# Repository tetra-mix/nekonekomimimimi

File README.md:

# ねこねこみみみみ
## 概要
VRCとの連携を目的として、市販されている猫耳カチューシャに取り付けられるハプティクスデバイスを作成する。ケーブル部分には、3Dプリンターで作成したケーブルチェーンを用いる。senseshift-hardwareというOSSプロジェクトを参考にしながら作成する。

## 参考
[自作ハプティクスベストを作ってみた。｜KirisameNanoha](https://note.com/kirisamenanoha/n/n8a3842eb5d57)
[GitHub - senseshift/senseshift-hardware: Hardware schematics to build haptic-feedback devices](https://github.com/senseshift/senseshift-hardware)
[OSC](https://note.com/kirisamenanoha/n/n18400ababb78?app_launch=false)
## 予備知識

### ハプティクスモーターについて
ERM 偏心回転質量
* PWAで制御
	種類
	* コイン型
	* 円筒型
	* コア型

LRA 線形共振
* 注意：ドライバが必要
	種類
	* コイン型
	* バー型
	* Y軸(平行)
	* Z軸(垂直)

## 案
### 案１
* マイコン esp32系
	* xiao esp32s3 or c6
* ドライバ DRV2605 x2
* LRAコイン型(Z軸)を直線に複数配置
* 左右の耳の下に3つずつ(計6つ)
* 電源をどうするかは検討
	* リポバッテリー？
	* 最初はモバイルバッテリーかな
→LRAが入手しづらい

### 案２ →採用
 * マイコン esp32系
	* xiao esp32s3 or c6
* ERMコイン型を直線に複数配置
* 左右の耳の下に3つずつ(計6つ)
* MOSFET x6
* 電源をどうするかは検討
	* リポバッテリー？
	* 最初はモバイルバッテリー

## 回路図
1チャンネル分
```
                 VMOTOR (+3.0V～4.2V)
                        |
                        |
                    +---+---+
                    |  ERM  |
                    |Motor  |
                    +---+---+
                        |
                        +-------------------+
                        |                   |
                        |                 |<| D1
                        |            SS14 / 1N5819
                        |                 | |
                        |                   |
                        |                   +---- VMOTOR
                        |
                      Drain
                    Q1 N-MOSFET ---- Gate
                      Source
                        |
                       GND

XIAO GPIO PWM ----[100Ω]---- Gate
                         |
                       [100kΩ]
                         |
                        GND
```

MOSFETをどれだけON・OFFするかによって強さを決める

## 配置図
```
        [前（おでこ）]

   左側               右側
   ●──●──●       ●──●──●
   前  中  後       前  中  後

        [後（後頭部）]
```

## 部品
秋月電子の場合

| 品名            | 型番                  |  個数 |    値段 | 購入リンク                                                  |
| ------------- | ------------------- | --: | ----: | ------------------------------------------------------ |
| DMOSトランジスタアレイ | TBD62003APG         |   1 |   100 | [109943](https://akizukidenshi.com/catalog/g/g109943/) |
| ミニ振動モーター      | (記載なし / 秋月ミニ振動モーター) |   6 |   200 | [16777](https://akizukidenshi.com/catalog/g/g116777/)  |
| マイコンボード       | XIAO ESP32S3        |   1 | 1,480 | [118078](https://akizukidenshi.com/catalog/g/g118078/) |
| ショットキーダイオード   | 1S4                 |   1 |   140 | [116384](https://akizukidenshi.com/catalog/g/g116384/) |
| 電解コンデンサ       | 1000µF（耐圧10V〜）      |   1 |    20 | [108424](https://akizukidenshi.com/catalog/g/g108424/) |
| LDO 3.3V1A    | BA033CC0T           |   1 |   100 | [113675](https://akizukidenshi.com/catalog/g/g113675/) |

合計3220円

振動モーターはアリエクで買ってもいいかも？

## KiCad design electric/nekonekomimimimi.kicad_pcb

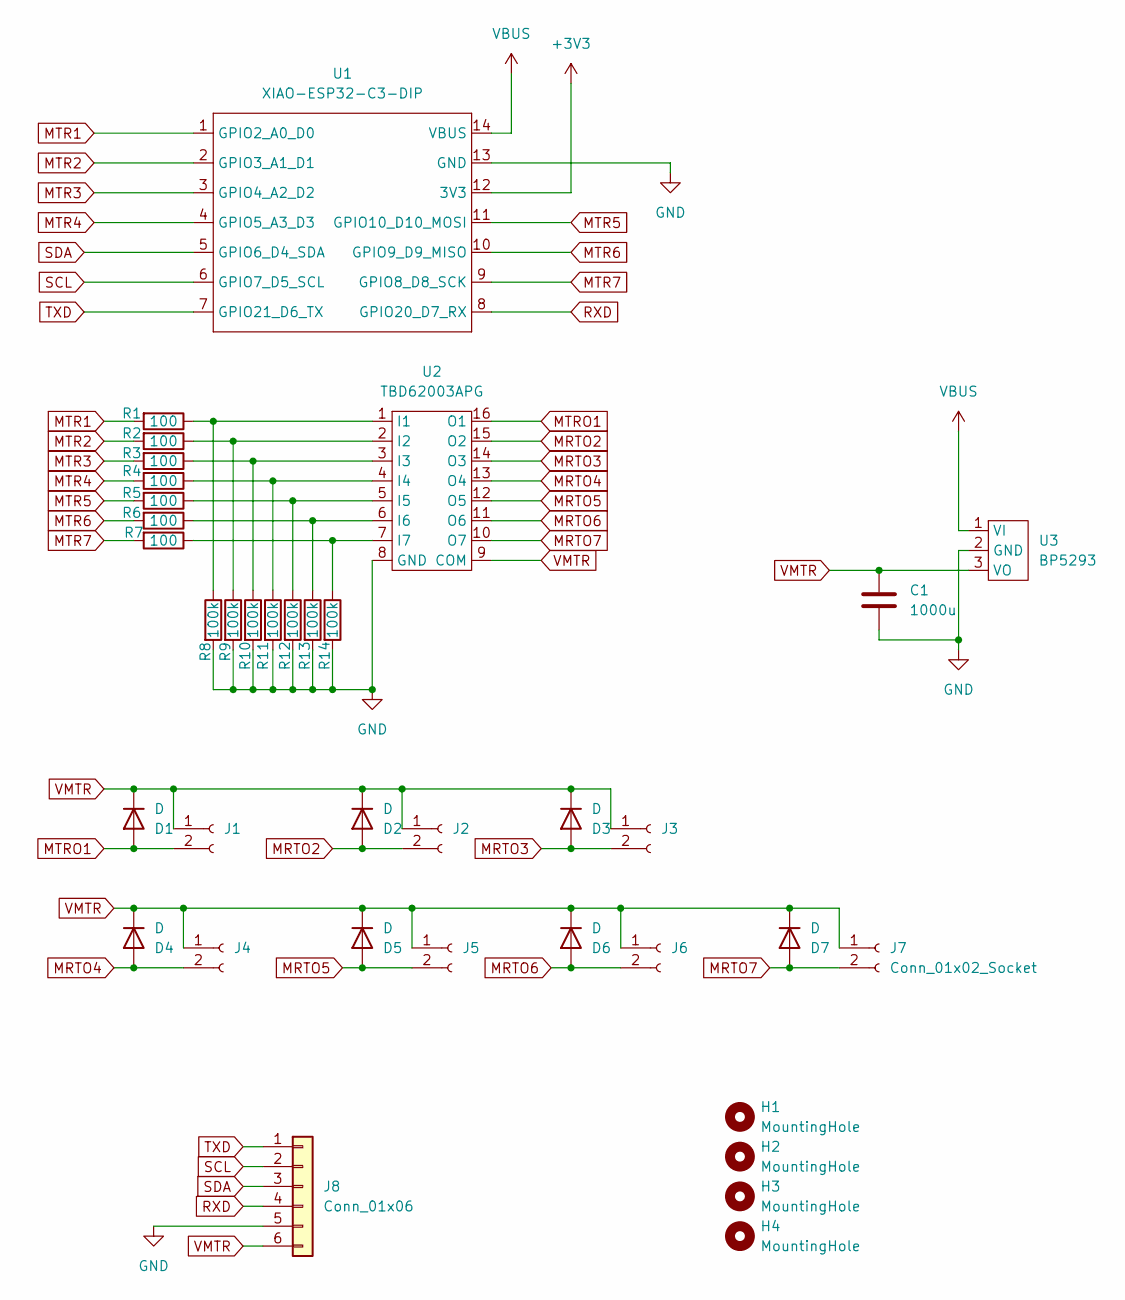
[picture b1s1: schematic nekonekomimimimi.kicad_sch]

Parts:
C1: 1000u; CP_Radial_D10.0mm_P5.00mm
D1, D2, D3, D4, D5, D6, D7: D; D_DO-35_SOD27_P7.62mm_Horizontal
H1, H2, H3, H4: MountingHole; MountingHole_2.2mm_M2
J1, J2, J3, J4, J5, J6, J7: Conn_01x02_Socket; JST_XH_B2B-XH-A_1x02_P2.50mm_Vertical
J8: Conn_01x06; PinHeader_1x06_P2.54mm_Vertical
R1, R2, R3, R4, R5, R6, R7: 100; resistor_0207_10
R8, R9, R10, R11, R12, R13, R14: 100k; resistor_0207_10
U1: XIAO-ESP32-C3-DIP; XIAO-ESP32-C6-DIP
U2: TBD62003APG; DIP-16_W7.62mm_Socket
U3: BP5293; PinHeader_1x03_P2.54mm_Vertical

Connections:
+3V3: U1.12 (3V3)
GND: C1.2, J8.5, R8.2, R9.2, R10.2, R11.2, R12.2, R13.2, R14.2, U1.13 (GND), U2.8 (GND), U3.2 (GND)
MRTO2: D2.2 (A), J2.2, U2.15 (O2)
MRTO3: D3.2 (A), J3.2, U2.14 (O3)
MRTO4: D4.2 (A), J4.2, U2.13 (O4)
MRTO5: D5.2 (A), J5.2, U2.12 (O5)
MRTO6: D6.2 (A), J6.2, U2.11 (O6)
MRTO7: D7.2 (A), J7.2, U2.10 (O7)
MTR1: R1.2, U1.1 (GPIO2_A0_D0)
MTR2: R2.2, U1.2 (GPIO3_A1_D1)
MTR3: R3.2, U1.3 (GPIO4_A2_D2)
MTR4: R4.2, U1.4 (GPIO5_A3_D3)
MTR5: R5.2, U1.11 (GPIO10_D10_MOSI)
MTR6: R6.2, U1.10 (GPIO9_D9_MISO)
MTR7: R7.2, U1.9 (GPIO8_D8_SCK)
MTRO1: D1.2 (A), J1.2, U2.16 (O1)
unnamed: R1.1, R8.1, U2.1 (I1)
unnamed: R2.1, R9.1, U2.2 (I2)
unnamed: R3.1, R10.1, U2.3 (I3)
unnamed: R4.1, R11.1, U2.4 (I4)
unnamed: R5.1, R12.1, U2.5 (I5)
unnamed: R6.1, R13.1, U2.6 (I6)
unnamed: R7.1, R14.1, U2.7 (I7)
RXD: J8.4, U1.8 (GPIO20_D7_RX)
SCL: J8.2, U1.6 (GPIO7_D5_SCL)
SDA: J8.3, U1.5 (GPIO6_D4_SDA)
TXD: J8.1, U1.7 (GPIO21_D6_TX)
VBUS: U1.14 (VBUS), U3.1 (VI)
VMTR: C1.1, D1.1 (K), D2.1 (K), D3.1 (K), D4.1 (K), D5.1 (K), D6.1 (K), D7.1 (K), J1.1, J2.1, J3.1, J4.1, J5.1, J6.1, J7.1, J8.6, U2.9 (COM), U3.3 (VO)

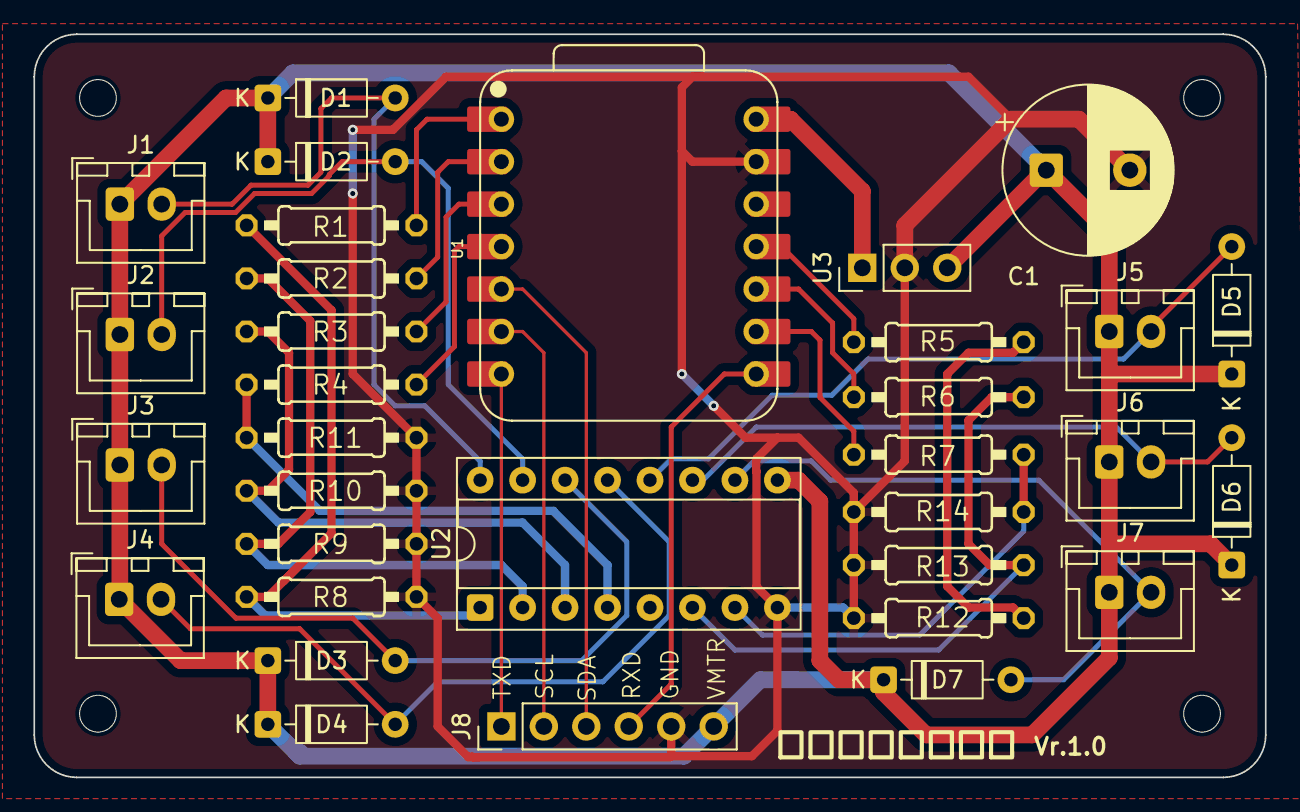
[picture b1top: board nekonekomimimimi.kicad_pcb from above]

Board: 2 copper layers, 73.7 x 44.5 mm, 37 parts (0 on the bottom side), 28 nets.

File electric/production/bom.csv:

Designator,Footprint,Quantity,Value,LCSC Part #
C1,CP_Radial_D10.0mm_P5.00mm,1,1000u,
"D1, D2, D3, D4, D5, D6, D7",D_DO-35_SOD27_P7.62mm_Horizontal,7,D,
"H1, H2, H3, H4",MountingHole_2.2mm_M2,4,MountingHole,
"J1, J2, J3, J4, J5, J6, J7",JST_XH_B2B-XH-A_1x02_P2.50mm_Vertical,7,Conn_01x02_Socket,
J8,PinHeader_1x06_P2.54mm_Vertical,1,Conn_01x06,
"R1, R2, R3, R4, R5, R6, R7",resistor_0207_10,7,100,
"R10, R11, R12, R13, R14, R8, R9",resistor_0207_10,7,100k,
U1,XIAO-ESP32-C6-DIP,1,XIAO-ESP32-C3-DIP,
U2,DIP-16_W7.62mm_Socket,1,TBD62003APG,
U3,PinHeader_1x03_P2.54mm_Vertical,1,BP5293,

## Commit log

2026-03-20 init
2026-03-20 title
2026-04-08 feat: electric
2026-04-08 update: build data
2026-04-08 update: update
2026-04-08 update: 3D files
2026-04-11 feat: 3D models
2026-04-19 faet: add 3D models
2026-05-05 update: add 3Dmodels
2026-05-07 update: change parts
2026-05-07 faet: hard osc program
2026-05-07 update: change folder name
2026-05-07 feat: hardware test program
